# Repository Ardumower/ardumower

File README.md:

# Ardumower

## Download
__WARNING__: Do not use the master version (via download button), that is 'code we work on' and it may be unstable - use one release version instead (click on 'releases' link below)!

https://github.com/Ardumower/ardumower/releases

## Reporting a bug / Fehler melden
[Click here!](https://github.com/Ardumower/ardumower/issues/new?title=Error+XYZ+%2F+Fehler+XYZ&body=Please+always+fill-in+below%2FBitte+unbedingt+ausf%C3%BCllen%21%0D%0A%0D%0A--English--%0D%0AYour+battery+voltage+%2812v%2C+24v%29%3A+24v%0D%0AYour+gear+motor+%28Ardumower%2C+other%29%3A+Ardumower+motor%0D%0AYour+Ardumower+software+version+%28pfodApp-%3EInfo%29%3A+890%0D%0AYour+Arduino+%28Mega+or+Due%29%3A+Mega+2560%0D%0AYour+PCB+version+%28printed+on+PCB%29%3A+0.5%0D%0AYour+PCB+mounted+parts+configuration+%28default+or+custom+and+how%29%3A+default%0D%0AOdometry+sensor+%28yes%2Fno%29%3F+yes%0D%0AArdumower+chassis+%28yes%2Fno%29%3F+yes%0D%0AExact+error+description%3A+...+%0D%0A%0D%0A--Deutsch--%0D%0ADeine+Akku-Spannung+%2812v%2C+24v%29%3A+24v%0D%0ADein+Antriebsmotor+%28Ardumower%2C+anderer%29%3A+Ardumower+Motor%0D%0ADeine+Ardumower-Software+Version%3A+%28pfodApp-%3EInfo%29%3A+890%0D%0ADeine+PCB-Version+%28siehe+Aufdruck%29%3A+0.5%0D%0ADein+Arduino+%28Mega+oder+Due%29%3A+Mega+2560%0D%0ADeine+PCB+Bauteilbest%C3%BCckung+%28Standard+oder+abweichend+und+wie%29%3A+Standard%0D%0AOdometrie+sensor+%28ja%2Fnein%29%3F+ja%0D%0AArdumower+Chassis+%28ja%2Fnein%29%3F+ja%0D%0AGenaue+Fehlerbeschreibung%3A+...%0D%0A) 

## Description
Develop an open source robotic lawn mower (HW+SW reference platform)

## Project site
http://www.ardumower.de

## Wiki site
http://wiki.ardumower.de

## This repository contains
* Ardumower robot code (Arduino code)
* Ardumower perimeter sender code (Arduino code)
* Ardumower PCB schematics (PDF, KiCAD)
* Ardumower simulator (requires CodeBlocks - see installation details here:  http://wiki.ardumower.de/index.php?title=Sensor_fusion#SLAM_simulation)
* Ardumower tests (MC33926, DS1307, LM386, HCSR04, GY-80, ESP8266, HB200A, MPU9150, HC-05, PfodApp)

## License
Ardumower (www.ardumower.de)
<br>Copyright (c) 2015-2017 by Uwe Zimprich
<br>Copyright (c) 2014-2015 by Stefan Manteuffel
<br>Copyright (c) 2014 by Walter Crauwels
<br>Copyright (c) 2013-2015 by Sven Gennat
<br>Copyright (c) 2013-2017 by Alexander Grau
<br>Copyright (c) 2014 by Maxime Carpentieri
<br>Copyright (c) 2015-2017 by Juergen Lange    

Private-use only! (you need to ask for a commercial-use)
 
The code/schematics/PCB files are open: you can modify it under the terms of the 
GNU General Public License as published by the Free Software Foundation, 
either version 3 of the License, or (at your option) any later version.

The code/schematics/PCB files are distributed in the hope that it will be useful,
but WITHOUT ANY WARRANTY; without even the implied warranty of
MERCHANTABILITY or FITNESS FOR A PARTICULAR PURPOSE.  See the
GNU General Public License for more details.

You should have received a copy of the GNU General Public License
along with this program.  If not, see <http://www.gnu.org/licenses/>.

Private-use only! (you need to ask for a commercial-use)

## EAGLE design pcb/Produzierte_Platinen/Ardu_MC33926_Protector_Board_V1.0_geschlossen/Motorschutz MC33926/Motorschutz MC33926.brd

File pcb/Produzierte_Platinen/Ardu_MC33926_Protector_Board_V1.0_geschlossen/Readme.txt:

Dises Projekt Ardu_MC33926_Protector_Board_V1.0_geschlossen 
wurde in Eagel gezeichnet und muss damit auch geöffnet werden.

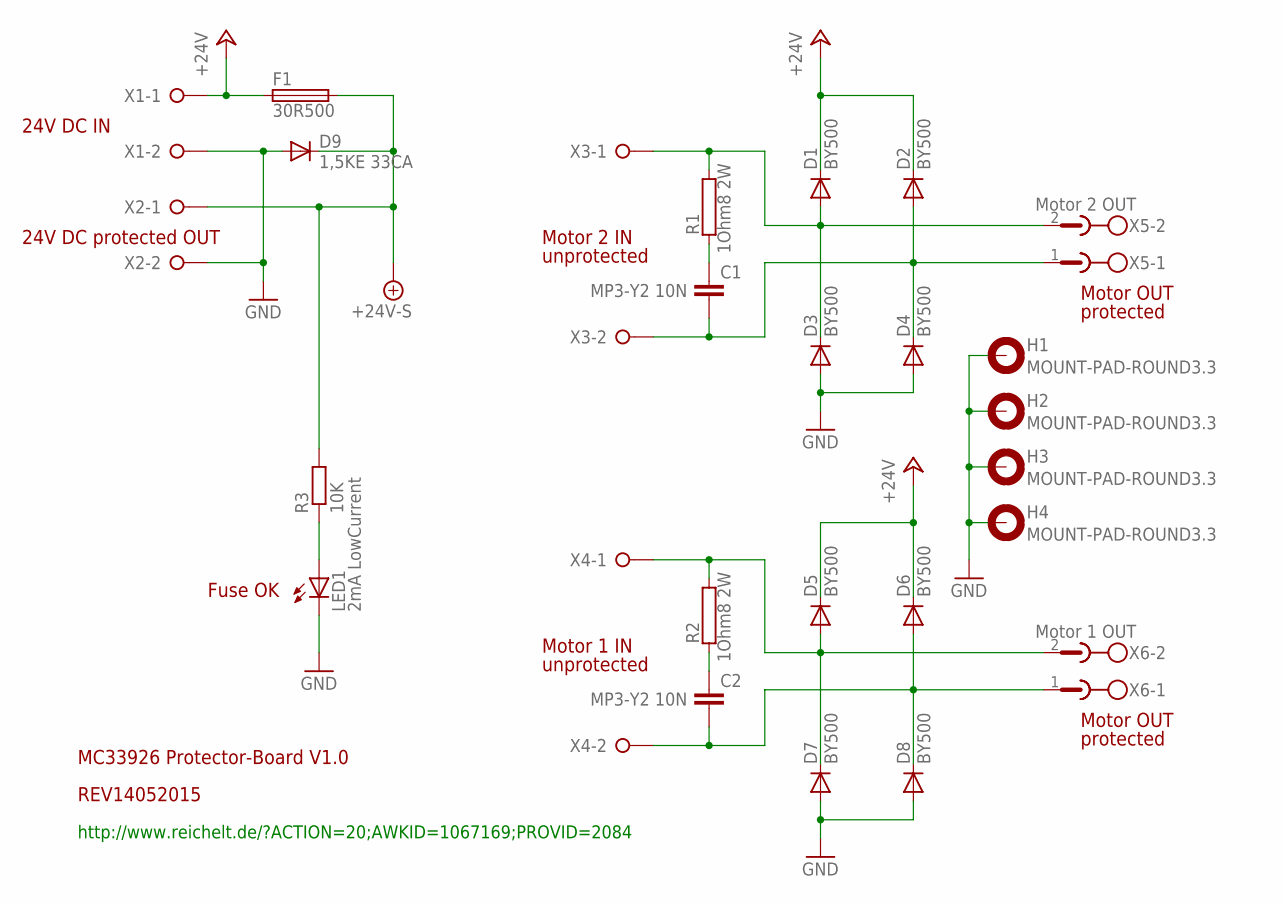
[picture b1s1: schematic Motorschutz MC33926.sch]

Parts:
C1, C2: MP3-Y2 10N; C15B5
D1, D2, D3, D4, D5, D6, D7, D8: BY500; DO201-15
D9: 1,5KE 33CA; DO201-15
F1: 30R500; LITTLEFUSE
H1, H2, H3, H4: MOUNT-PAD-ROUND3.3; 3,3-PAD
LED1: 2mA LowCurrent; LED5MM
R1, R2: 1Ohm8 2W; AC07
R3: 10K; 0204/7
X1, X2, X3, X4: W237-02P; W237-132
X5: Motor 2 OUT; MSTBV2
X6: Motor 1 OUT; MSTBV2

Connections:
+24V: D1.C, D2.C, D5.C, D6.C, F1.1, X1.1
+24V-S: D9.C, F1.2, R3.2, X2.1
GND: D3.A, D4.A, D7.A, D8.A, D9.A, H1.B3,3, H2.B3,3, H3.B3,3, H4.B3,3, LED1.K (C), X1.2, X2.2
unnamed: D5.A, D7.C, R2.2, X4.1, X6.2
unnamed: C2.1, R2.1
unnamed: C2.2, D6.A, D8.C, X4.2, X6.1
unnamed: D1.A, D3.C, R1.2, X3.1, X5.2
unnamed: C1.2, D2.A, D4.C, X3.2, X5.1
unnamed: C1.1, R1.1
unnamed: LED1.A, R3.1

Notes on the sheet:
MC33926 Protector-Board V1.0
REV14052015
24V DC IN
24V DC protected OUT
Motor 2 IN
Motor 1 IN
Fuse OK
unprotected
protected
Motor OUT
http://www.reichelt.de/?ACTION=20;AWKID=1067169;PROVID=2084

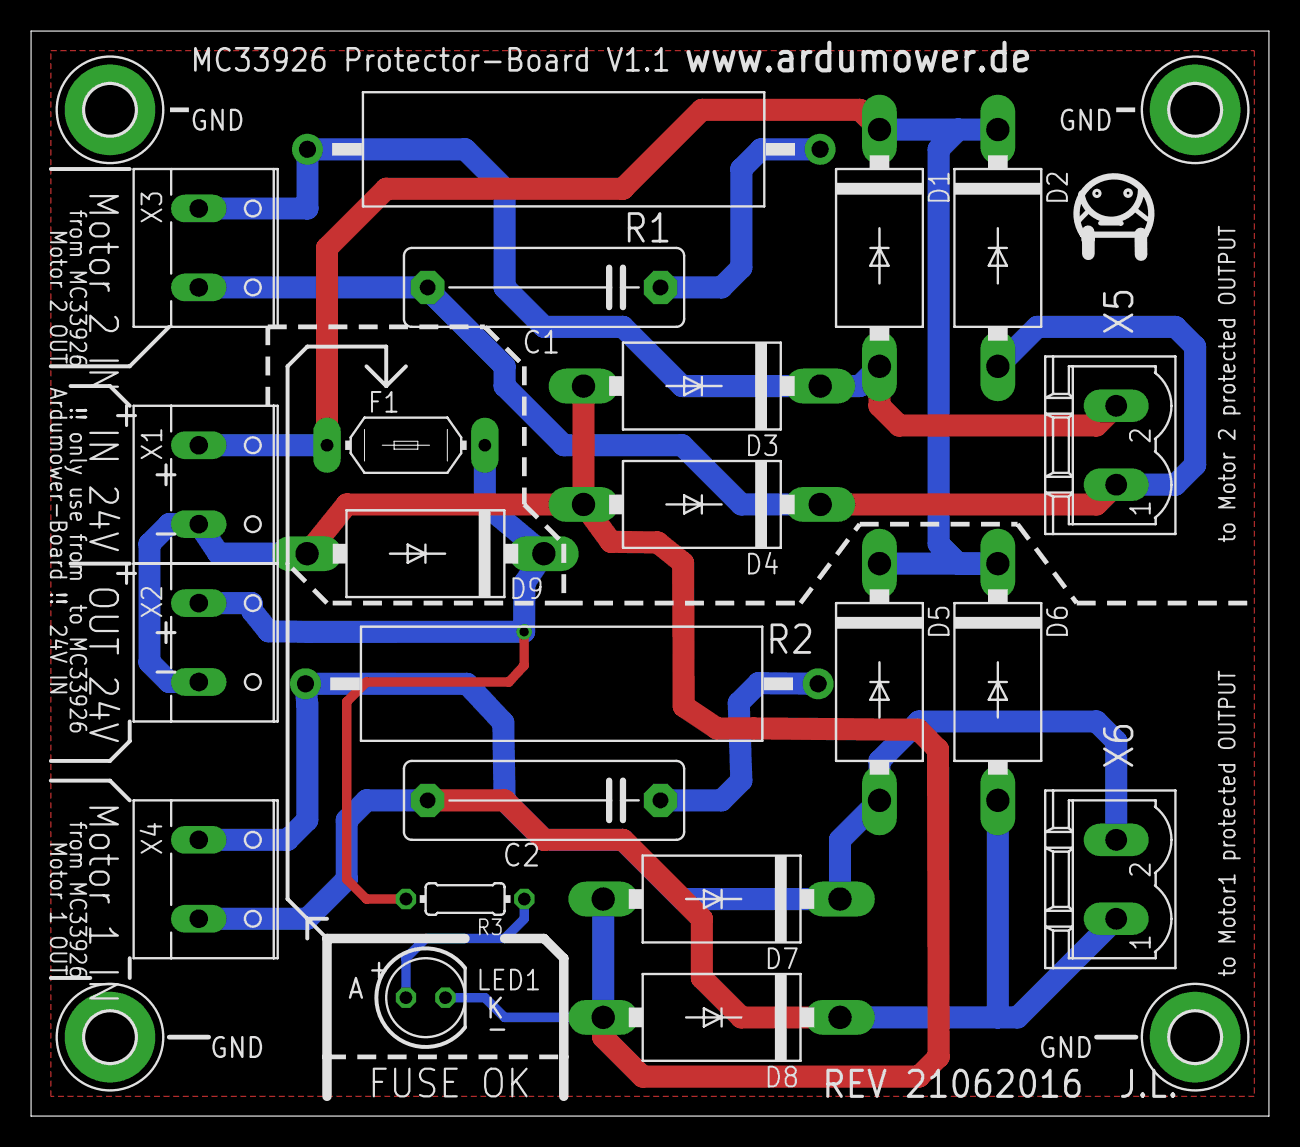
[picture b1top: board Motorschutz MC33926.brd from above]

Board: 2 copper layers, 79.7 x 69.8 mm, 26 parts (0 on the bottom side), 10 nets.

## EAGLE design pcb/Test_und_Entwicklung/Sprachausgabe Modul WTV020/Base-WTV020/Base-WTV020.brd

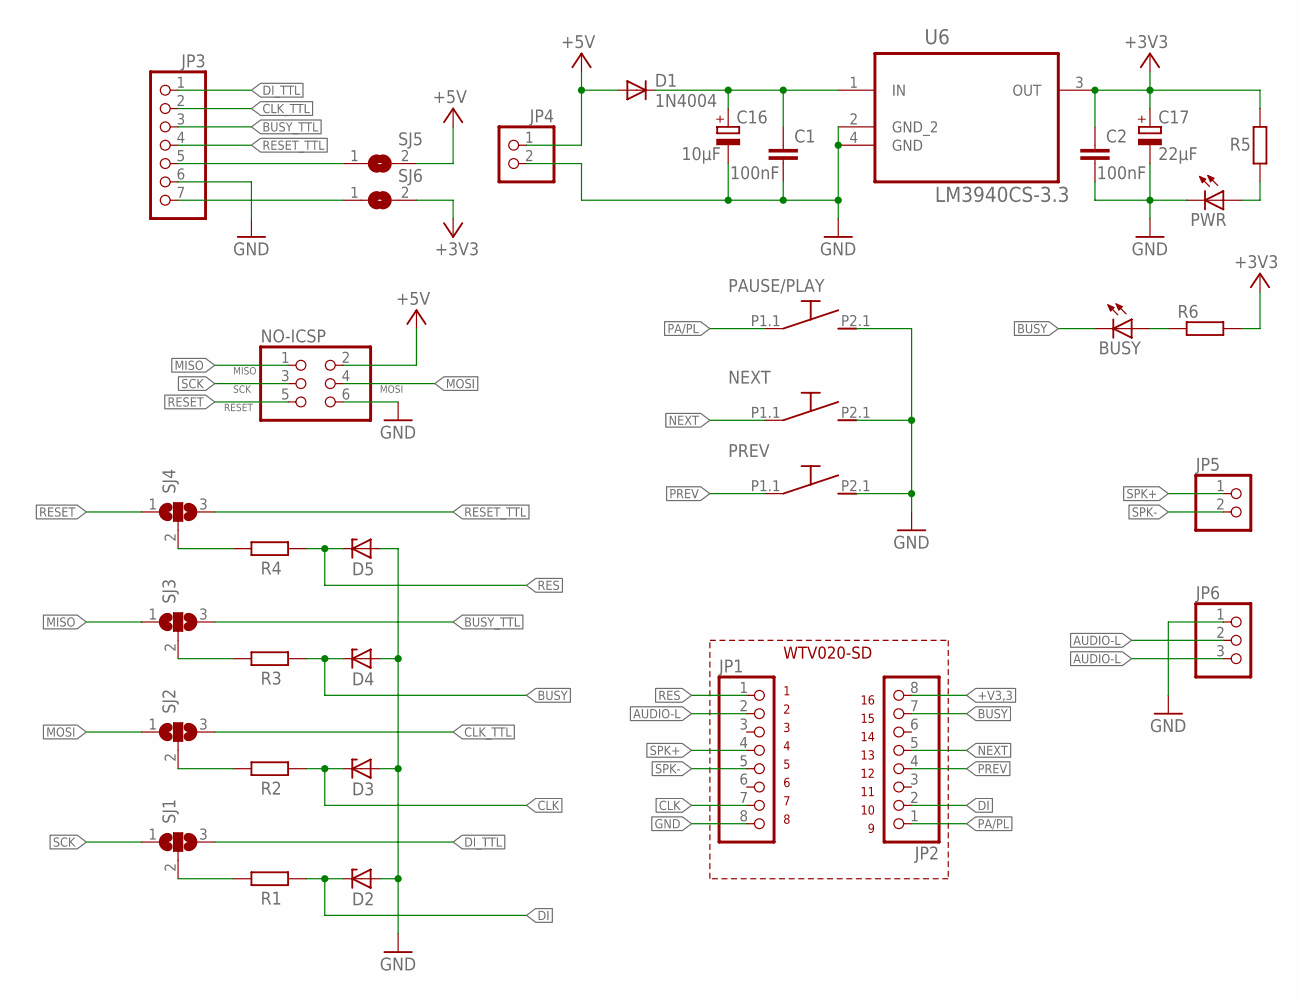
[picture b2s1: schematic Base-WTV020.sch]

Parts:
BUSY: LED3MM
C1, C2: 100nF; C0805
C16: 10µF; E2,5-5
C17: 22µF; E2,5-5
D1: 1N4004; DO41-10
D2, D3, D4, D5: ZENER-DIODESOD80C; SOD80C
JP1, JP2: PINHD-1X8; 1X08
JP3: PINHD-1X7; 1X07
JP4, JP5: PINHD-1X2; 1X02
JP6: PINHD-1X3; 1X03
NEXT: SMDTASTE
NO-ICSP: PINHD-2X3; 2X03
PAUSE/PLAY: SMDTASTE
PREV: SMDTASTE
PWR: LED3MM
R1, R2, R3, R4, R5, R6: R-EU_M1206; M1206
SJ1, SJ2, SJ3, SJ4: SJ2W; SJ_2
SJ5, SJ6: SJ
U6: LM3940CS-3.3; TO254P1435X464-4N

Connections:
+5V: D1.A, JP4.1, NO-ICSP.2, SJ5.2
+V3,3: C2.1, C17.+, JP2.8, R5.2, R6.2, SJ6.2, U6.3 (OUT)
AUDIO-L: JP1.2, JP6.2, JP6.3
BUSY: BUSY.K (C), D4.C, JP2.7, R3.1
BUSY_TTL: JP3.3, SJ3.3
CLK: D3.C, JP1.7, R2.1
CLK_TTL: JP3.2, SJ2.3
DI: D2.C, JP2.2, R1.1
DI_TTL: JP3.1, SJ1.3
GND: C1.2, C2.2, C16.-, C17.-, D2.A, D3.A, D4.A, D5.A, JP1.8, JP3.6, JP4.2, JP6.1, NEXT.P2.1 (2), NO-ICSP.6, PAUSE/PLAY.P2.1 (2), PREV.P2.1 (2), PWR.K (C), U6.2 (GND_2), U6.4 (GND)
MISO: NO-ICSP.1, SJ3.1
MOSI: NO-ICSP.4, SJ2.1
unnamed: PWR.A, R5.1
unnamed: BUSY.A, R6.1
unnamed: R1.2, SJ1.2
unnamed: R2.2, SJ2.2
unnamed: R3.2, SJ3.2
unnamed: R4.2, SJ4.2
unnamed: C1.1, C16.+, D1.C, U6.1 (IN)
unnamed: JP3.5, SJ5.1
unnamed: JP3.7, SJ6.1
NEXT: JP2.5, NEXT.P1.1 (1)
PA/PL: JP2.1, PAUSE/PLAY.P1.1 (1)
PREV: JP2.4, PREV.P1.1 (1)
RES: D5.C, JP1.1, R4.1
RESET: NO-ICSP.5, SJ4.1
RESET_TTL: JP3.4, SJ4.3
SCK: NO-ICSP.3, SJ1.1
SPK+: JP1.4, JP5.1
SPK-: JP1.5, JP5.2

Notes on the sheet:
WTV020-SD

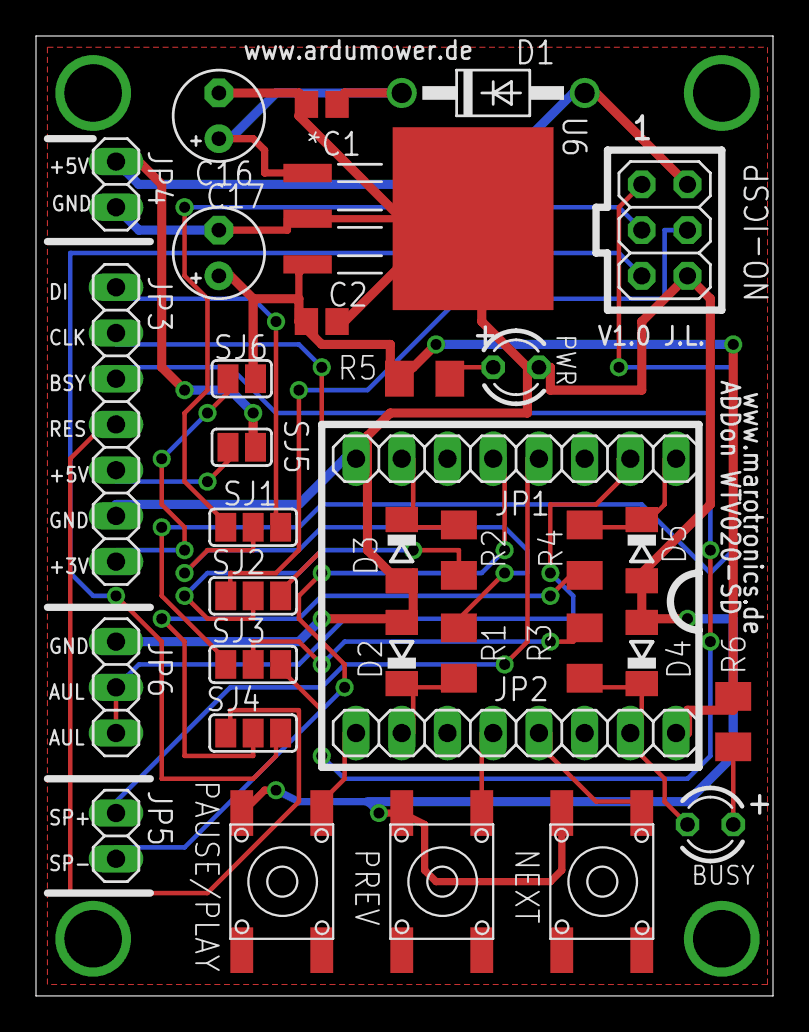
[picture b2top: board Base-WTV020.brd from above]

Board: 2 copper layers, 40.9 x 53.3 mm, 34 parts (0 on the bottom side), 30 nets.

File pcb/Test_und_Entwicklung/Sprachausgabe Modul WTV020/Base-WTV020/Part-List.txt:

Partlist

Exported from Base-WTV020.sch at 29.03.2016 22:23:30

EAGLE Version 6.4.0 Copyright (c) 1988-2013 CadSoft

Assembly variant: 

Part       Value          Device            Package           Library      Sheet

BUSY                      LED3MM 2mA        LED3MM            led          1
C1         100nF          C-EUC0805         C0805             resistor     1
C2         100nF          C-EUC0805         C0805             resistor     1
C16        10µF           CPOL-EUE2.5-5     E2,5-5            resistor     1
C17        22µF           CPOL-EUE2.5-5     E2,5-5            resistor     1
D1         1N4004         1N4004            DO41-10           diode        1
D2         3,3V           ZENER-DIODESOD80C SOD80C            diode        1
D3         3,3V           ZENER-DIODESOD80C SOD80C            diode        1
D4         3,3V           ZENER-DIODESOD80C SOD80C            diode        1
D5         3,3V           ZENER-DIODESOD80C SOD80C            diode        1
JP1                       PINHD-1X8         1X08              pinhead      1
JP2                       PINHD-1X8         1X08              pinhead      1
JP3                       PINHD-1X7         1X07              pinhead      1
JP4                       PINHD-1X2         1X02              pinhead      1
JP5                       PINHD-1X2         1X02              pinhead      1
JP6                       PINHD-1X3         1X03              pinhead      1
NEXT                      SMDTASTE          SMDTASTE          SMD-Taster   1
NO-ICSP                   PINHD-2X3         2X03              SmartPrj     1
PAUSE/PLAY                SMDTASTE          SMDTASTE          SMD-Taster   1
PREV                      SMDTASTE          SMDTASTE          SMD-Taster   1
PWR                       LED3MM 2mA        LED3MM            led          1
R1         1K             R-EU_M1206        M1206             resistor     1
R2         1K             R-EU_M1206        M1206             resistor     1
R3         1K             R-EU_M1206        M1206             resistor     1
R4         1K             R-EU_M1206        M1206             resistor     1
R5         330            R-EU_M1206        M1206             resistor     1
R6         330            R-EU_M1206        M1206             resistor     1
SJ1                       SJ2W              SJ_2              jumper       1
SJ2                       SJ2W              SJ_2              jumper       1
SJ3                       SJ2W              SJ_2              jumper       1
SJ4                       SJ2W              SJ_2              jumper       1
SJ5                       SJ                SJ                jumper       1
SJ6                       SJ                SJ                jumper       1
U6         LM3940CS-3.3   LM2940CS-5.0      TO254P1435X464-4N LM2940CS-5.0 1

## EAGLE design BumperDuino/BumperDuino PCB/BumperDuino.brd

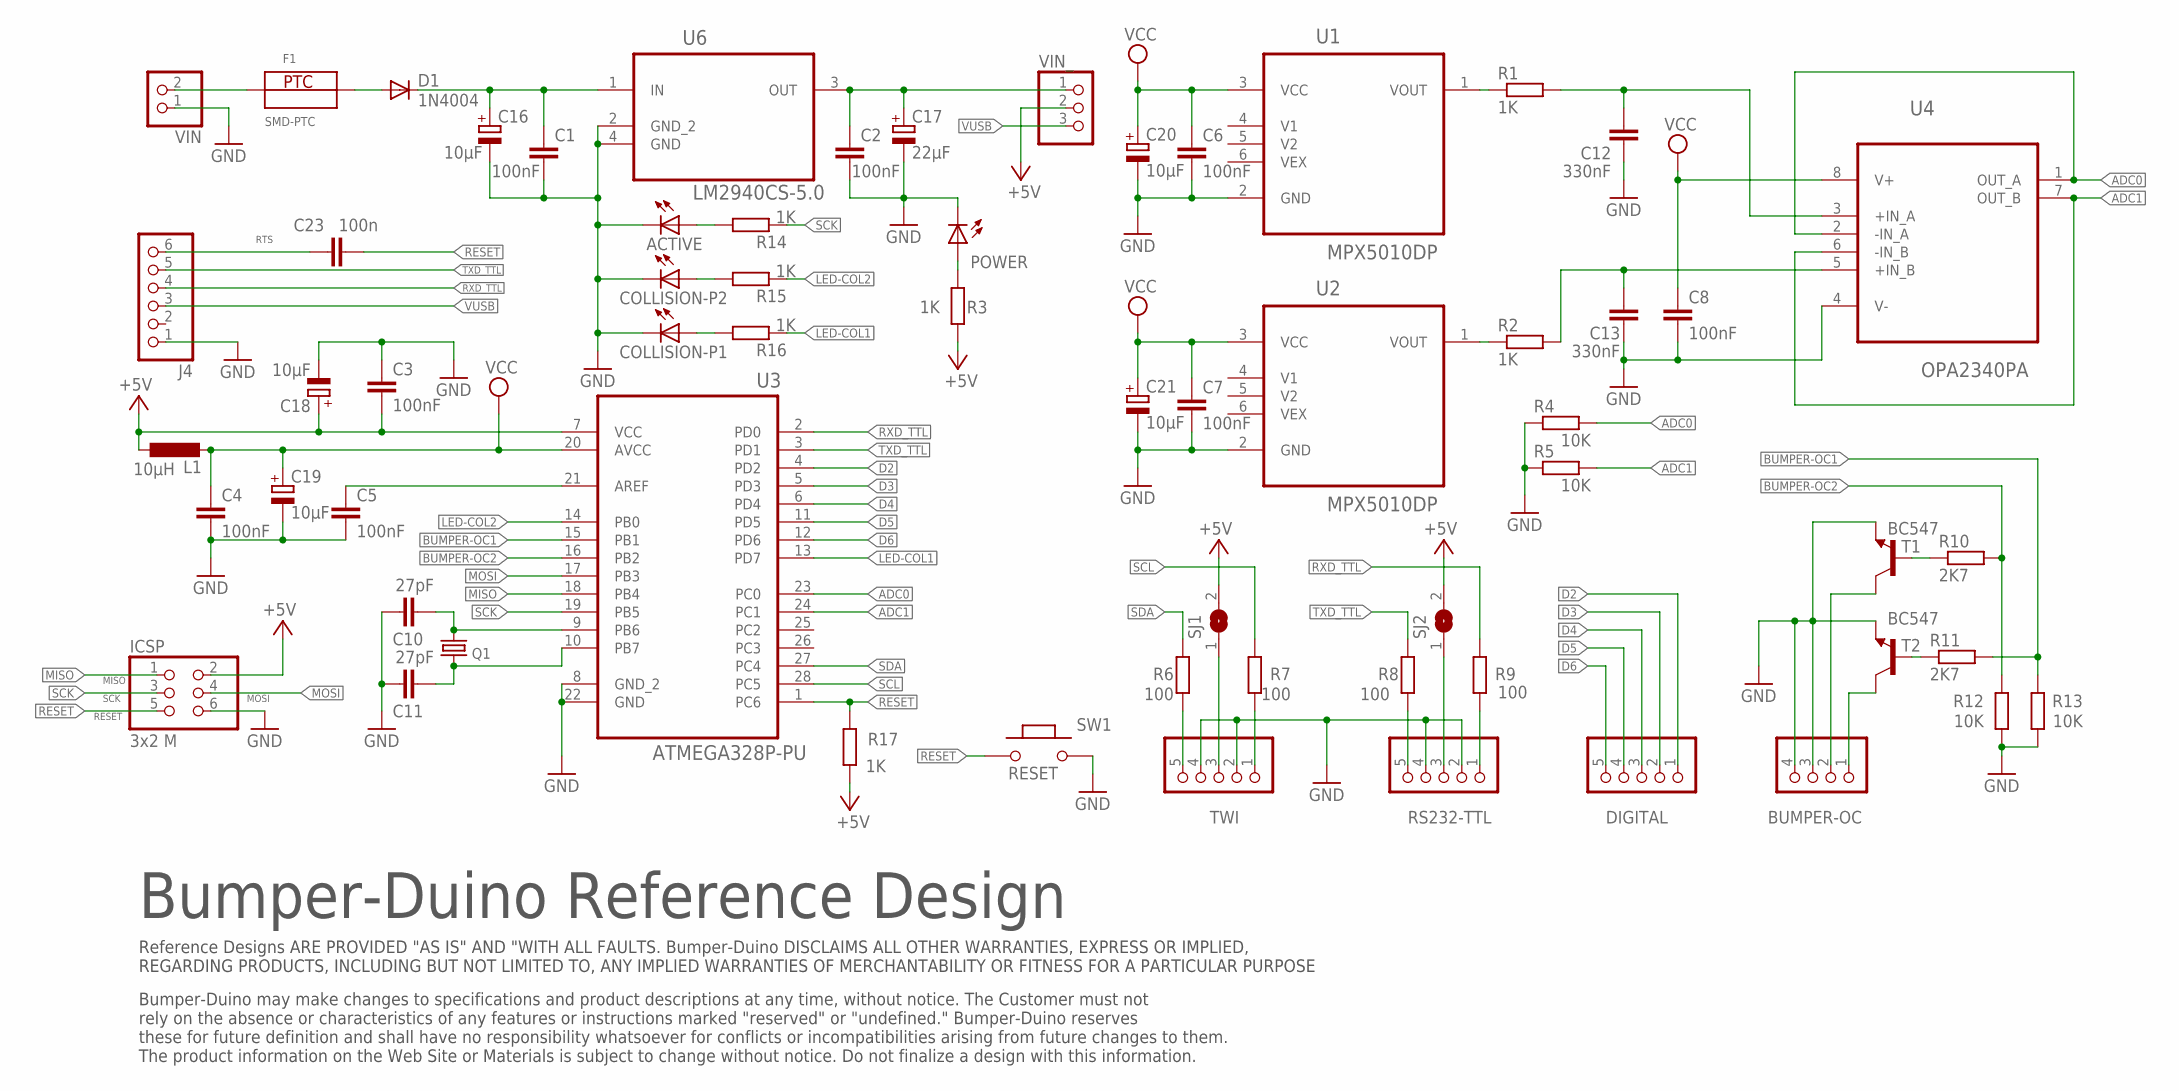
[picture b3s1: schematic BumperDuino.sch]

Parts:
ACTIVE: LED3MM
BUMPER-OC: PINHD-1X4; 1X04
C1, C2, C3, C4, C5, C6, C7, C8: 100nF; C025-025X050
C10, C11: 27pF; C025-025X050
C12, C13: 330nF; C025_050-035X075
C16, C18, C19, C20, C21: 10µF; E2,5-5
C17: 22µF; E2,5-5
C23: 100n; C025-025X050
COLLISION-P1, COLLISION-P2: LED3MM
D1: 1N4004; DO41-10
DIGITAL: PINHD-1X5; 1X05
F1: SMD-PTC
ICSP: 3x2 M; 2X03
J4: 6x1F Low profile (machined); 1X06-TH
L1: 10µH; 0204/7
POWER: LED3MM
Q1: HC49/S
R1, R2, R3, R14, R15, R16, R17: 1K; R1206
R4, R5, R12, R13: 10K; R1206
R6, R7, R8, R9: 100; R1206
R10, R11: 2K7; R1206
RS232-TTL: PINHD-1X5; 1X05
SJ1, SJ2: SJW
SW1: RESET; 157SW
T1, T2: BC547; TO92
TWI: PINHD-1X5; 1X05
U1, U2: MPX5010DP; FREESCALE_CASE_867C-05
U3: ATMEGA328P-PU; DIP254P762X457-28
U4: OPA2340PA; DIP254P762X508-8
U6: LM2940CS-5.0; TO254P1435X464-4N
VIN: PINHD-1X2; 1X02
VIN_: PINHD-1X3; 1X03

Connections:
ADC0: R4.2, U3.23 (PC0), U4.1 (OUT_A), U4.2 (-IN_A)
ADC1: R5.2, U3.24 (PC1), U4.6 (-IN_B), U4.7 (OUT_B)
BUMPER-OC1: R11.2, R13.2, U3.15 (PB1)
BUMPER-OC2: R10.2, R12.2, U3.16 (PB2)
D2: DIGITAL.1, U3.4 (PD2)
D3: DIGITAL.2, U3.5 (PD3)
D4: DIGITAL.3, U3.6 (PD4)
D5: DIGITAL.4, U3.11 (PD5)
D6: DIGITAL.5, U3.12 (PD6)
GND: ACTIVE.K (C), BUMPER-OC.3, BUMPER-OC.4, C1.2, C2.2, C3.1, C4.2, C5.2, C6.2, C7.2, C8.2, C10.1, C11.1, C12.2, C13.2, C16.-, C17.-, C18.-, C19.-, C20.-, C21.-, COLLISION-P1.K (C), COLLISION-P2.K (C), ICSP.6, J4.1, POWER.K (C), R4.1, R5.1, R12.1, R13.1, RS232-TTL.2, RS232-TTL.4, SW1.2, T1.1 (E), T2.1 (E), TWI.2, TWI.4, U1.2 (GND), U2.2 (GND), U3.8 (GND_2), U3.22 (GND), U4.4 (V-), U6.2 (GND_2), U6.4 (GND), VIN.1
LED-COL1: R16.1, U3.13 (PD7)
LED-COL2: R15.1, U3.14 (PB0)
MISO: ICSP.1, U3.18 (PB4)
MOSI: ICSP.4, U3.17 (PB3)
unnamed: C10.2, Q1.2, U3.9 (PB6)
unnamed: C11.2, Q1.1, U3.10 (PB7)
unnamed: R1.1, U1.1 (VOUT)
unnamed: R2.1, U2.1 (VOUT)
unnamed: C1.1, C16.+, D1.C, U6.1 (IN)
unnamed: C2.1, C17.+, U6.3 (OUT), VIN_.1
unnamed: C5.1, U3.21 (AREF)
unnamed: C12.1, R1.2, U4.3 (+IN_A)
unnamed: C13.1, R2.2, U4.5 (+IN_B)
unnamed: ACTIVE.A, R14.2
unnamed: COLLISION-P2.A, R15.2
unnamed: D1.A, F1.2
unnamed: F1.1, VIN.2
unnamed: POWER.A, R3.2
unnamed: COLLISION-P1.A, R16.2
unnamed: R6.1, TWI.5
unnamed: R7.1, TWI.1
unnamed: R8.1, RS232-TTL.5
unnamed: R9.1, RS232-TTL.1
unnamed: BUMPER-OC.1, T2.3 (C)
unnamed: BUMPER-OC.2, T1.3 (C)
unnamed: SJ1.1, TWI.3
unnamed: R11.1, T2.2 (B)
unnamed: R10.1, T1.2 (B)
unnamed: RS232-TTL.3, SJ2.1
RESET: C23.1, ICSP.5, R17.2, SW1.1, U3.1 (PC6)
RTS: C23.2, J4.6
RXD_TTL: J4.4, R9.2, U3.2 (PD0)
SCK: ICSP.3, R14.1, U3.19 (PB5)
SCL: R7.2, U3.28 (PC5)
SDA: R6.2, U3.27 (PC4)
TXD_TTL: J4.5, R8.2, U3.3 (PD1)
V5+: C3.2, C18.+, ICSP.2, L1.1, R3.1, R17.1, SJ1.2, SJ2.2, U3.7 (VCC), VIN_.2
VCC: C4.1, C6.1, C7.1, C8.1, C19.+, C20.+, C21.+, L1.2, U1.3 (VCC), U2.3 (VCC), U3.20 (AVCC), U4.8 (V+)
VUSB: J4.3, VIN_.3

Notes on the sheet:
Bumper-Duino Reference Design
Bumper-Duino may make changes to specifications and product descriptions at any time, without notice. The Customer must not rely on the absence or characteristics of any features or instructions marked "reserved" or "undefined." Bumper-Duino reserves these for future definition and shall have no re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
Reference Designs ARE PROVIDED "AS IS" AND "WITH ALL FAULTS. Bumper-Duino DISCLAIMS ALL OTHER WARRANTIES, EXPRESS OR IMPLIED, REGARDING PRODUCTS, INCLUDING BUT NOT LIMITED TO, ANY IMPLIED WARRANTIES OF MERCHANTABILITY OR FITNESS FOR A PARTICULAR PURPOSE

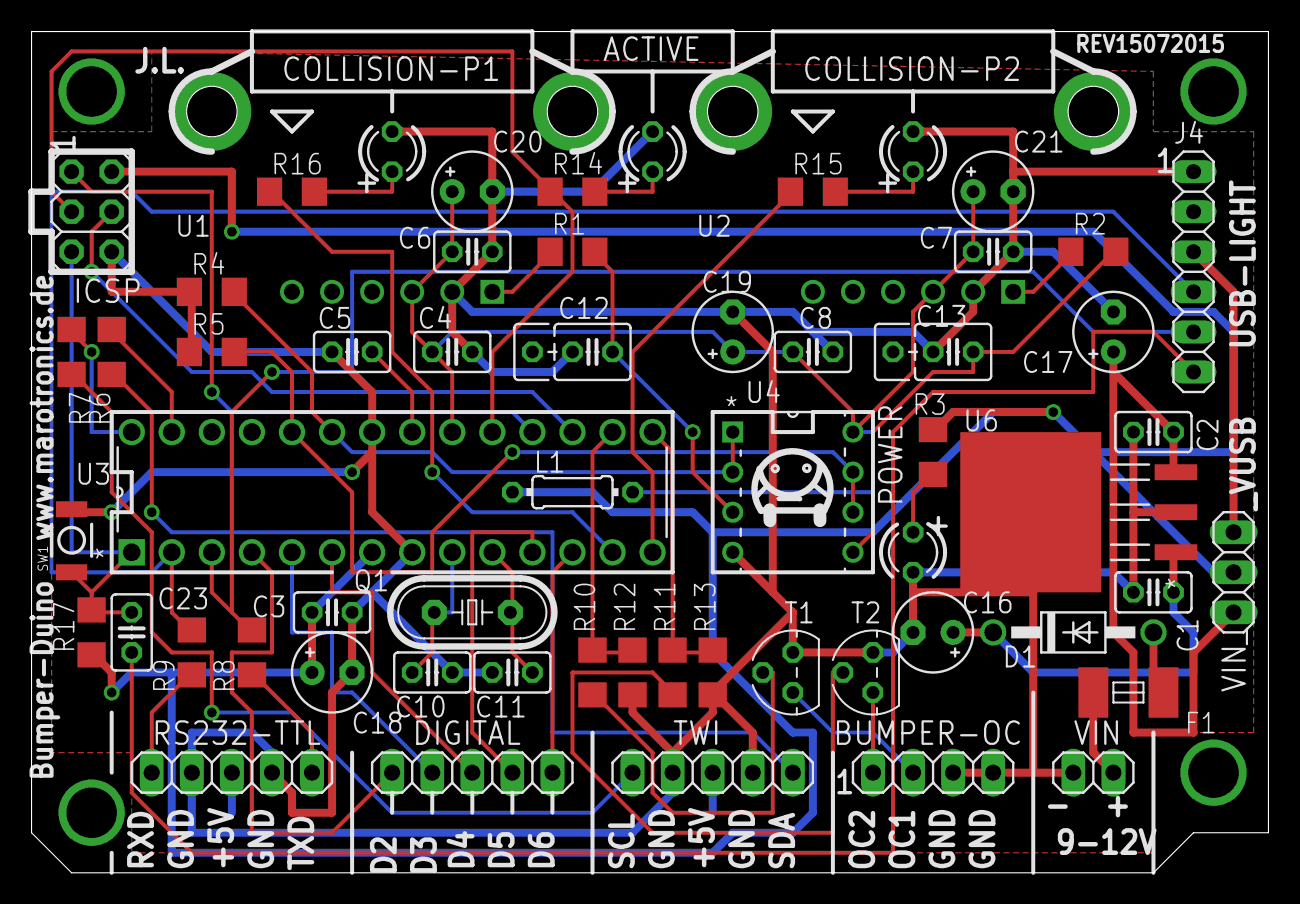
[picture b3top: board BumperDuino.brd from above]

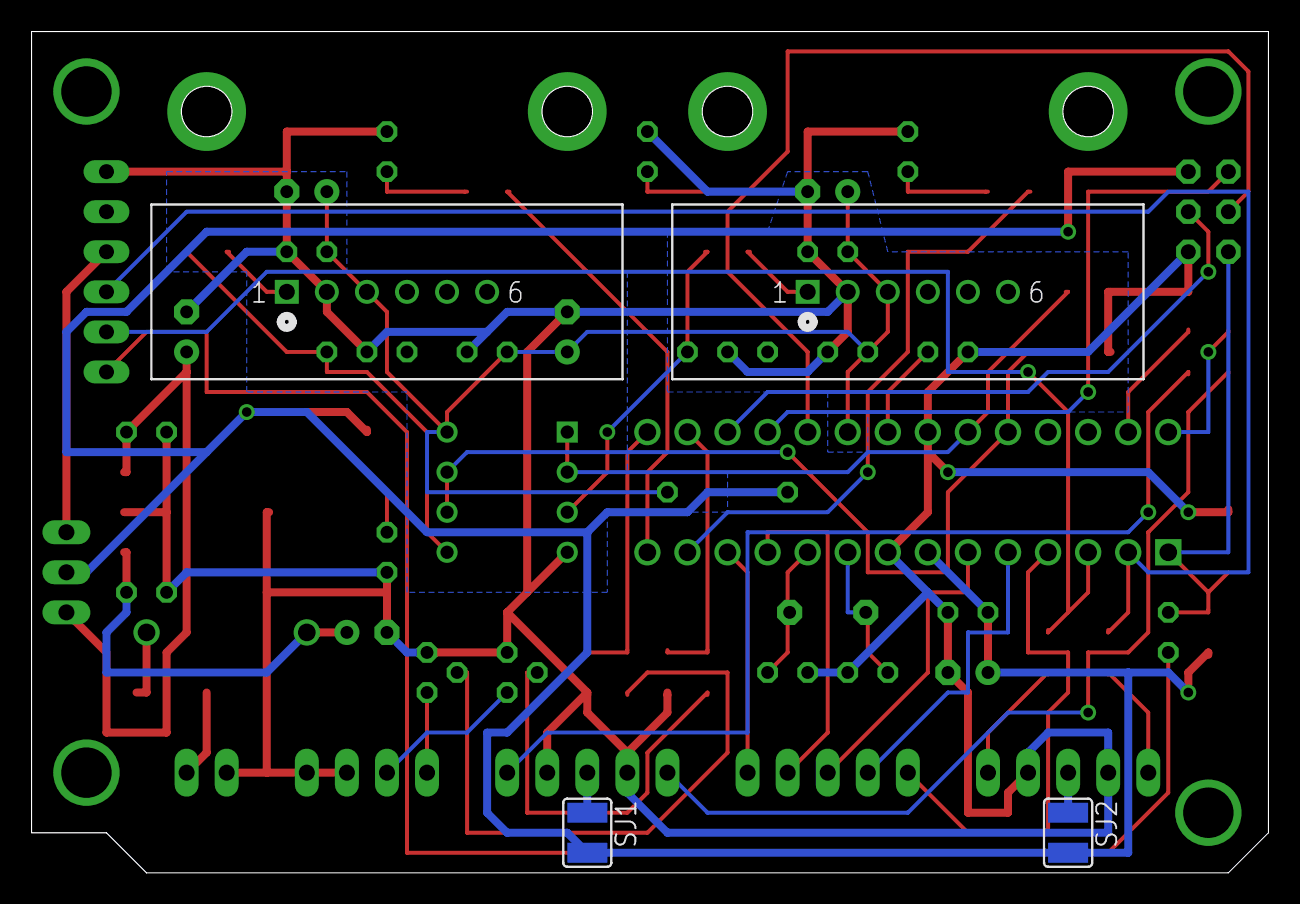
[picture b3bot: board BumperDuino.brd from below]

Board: 2 copper layers, 78.4 x 53.3 mm, 62 parts (4 on the bottom side), 49 nets.

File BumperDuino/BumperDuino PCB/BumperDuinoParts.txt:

Partlist

Exported from BumperDuino.brd at 30.07.2015 18:01:02

EAGLE Version 6.4.0 Copyright (c) 1988-2013 CadSoft

Assembly variant: 

Part         Value                       Package                Library                       Position (mm)         Orientation

ACTIVE                                   LED3MM                 led                           (50.8 72.39)          R90
BUMPER-OC                                1X04                   pinhead                       (68.58 33.02)         R0
C1           100nF                       C025-025X050           resistor                      (82.55 44.45)         R180
C2           100nF                       C025-025X050           resistor                      (82.55 54.61)         R180
C3           100nF                       C025-025X050           resistor                      (30.48 43.18)         R180
C4           100nF                       C025-025X050           resistor                      (38.1 59.69)          R0
C5           100nF                       C025-025X050           resistor                      (31.75 59.69)         R180
C6           100nF                       C025-025X050           resistor                      (39.37 66.04)         R0
C7           100nF                       C025-025X050           resistor                      (72.39 66.04)         R0
C8           100nF                       C025-025X050           resistor                      (60.96 59.69)         R0
C10          27pF                        C025-025X050           resistor                      (36.83 39.37)         R180
C11          27pF                        C025-025X050           resistor                      (41.91 39.37)         R0
C12          330nF                       C025_050-035X075       resistor                      (46.99 59.69)         R180
C13          330nF                       C025_050-035X075       resistor                      (69.85 59.69)         R180
C16          10µF                        E2,5-5                 resistor                      (68.58 41.91)         R180
C17          22µF                        E2,5-5                 resistor                      (80.01 60.96)         R90
C18          10µF                        E2,5-5                 resistor                      (30.48 39.37)         R0
C19          10µF                        E2,5-5                 resistor                      (55.88 60.96)         R90
C20          10µF                        E2,5-5                 resistor                      (39.37 69.85)         R0
C21          10µF                        E2,5-5                 resistor                      (72.39 69.85)         R0
C23          100n                        C025-025X050           resistor                      (17.78 41.91)         R270
COLLISION-P1                             LED3MM                 led                           (34.29 72.39)         R90
COLLISION-P2                             LED3MM                 led                           (67.31 72.39)         R90
D1           1N4004                      DO41-10                diode                         (77.47 41.91)         R0
DIGITAL                                  1X05                   pinhead                       (39.37 33.02)         R0
F1           SMD-PTC                     SMD-PTC                Sicherungen Siba              (78.74 38.1)          R0
ICSP         3x2 M                       2X03                   SmartPrj                      (15.24 68.58)         R270
J4           6x1F Low profile (machined) 1X06-TH                SmartPrj                      (85.09 64.77)         R270
L1           10µH                        0204/7                 resistor                      (45.72 50.8)          R0
POWER                                    LED3MM                 led                           (67.31 46.99)         R270
Q1                                       HC49/S                 quartz                        (39.37 43.18)         R180
R1           1K                          R1206                  resistor                      (45.72 66.04)         R0
R2           1K                          R1206                  resistor                      (78.74 66.04)         R0
R3           1K                          R1206                  resistor                      (68.58 53.34)         R270
R4           10K                         R1206                  resistor                      (22.86 63.5)          R0
R5           10K                         R1206                  resistor                      (22.86 59.69)         R0
R6           100                         R1206                  resistor                      (16.51 59.69)         R90
R7           100                         R1206                  resistor                      (13.97 59.69)         R90
R8           100                         R1206                  resistor                      (25.4 40.64)          R90
R9           100                         R1206                  resistor                      (21.59 40.64)         R90
R10          2K7                         R1206                  resistor                      (46.99 39.37)         R90
R11          2K7                         R1206                  resistor                      (52.07 39.37)         R90
R12          10K                         R1206                  resistor                      (49.53 39.37)         R90
R13          10K                         R1206                  resistor                      (54.61 39.37)         R90
R14          1K                          R1206                  resistor                      (45.72 69.85)         R0
R15          1K                          R1206                  resistor                      (60.96 69.85)         R0
R16          1K                          R1206                  resistor                      (27.94 69.85)         R0
R17          1K                          R1206                  resistor                      (15.24 41.91)         R90
RS232-TTL                                1X05                   pinhead                       (24.13 33.02)         R0
SJ1                                      SJW                    jumper                        (54.61 29.21)         MR270
SJ2                                      SJW                    jumper                        (24.13 29.21)         MR270
SW1          RESET                       157SW                  MySMD                         (13.97 45.72)         R90
T1           BC547                       TO92                   transistor                    (59.69 39.37)         R90
T2           BC547                       TO92                   transistor                    (64.77 39.37)         R90
TWI                                      1X05                   pinhead                       (54.61 33.02)         R0
U1           MPX5010DP                   FREESCALE_CASE_867C-05 MXP5010DP                     (27.94 63.5)          MR0
U2           MPX5010DP                   FREESCALE_CASE_867C-05 MXP5010DP                     (60.96 63.5)          MR0
U3           ATMEGA328P-PU               DIP254P762X457-28      Atmel_By_element14_Batch_1-00 (50.8 54.61)          R90
U4           OPA2340PA                   DIP254P762X508-8       OPA2340PA                     (63.5 46.99)          R0
U6           LM2940CS-5.0                TO254P1435X464-4N      LM2940CS-5.0                  (74.93 49.53)         R90
VIN                                      1X02                   pinhead                       (78.74 33.02)         R0
VIN_                                     1X03                   pinhead                       (87.63 45.72)         R90
